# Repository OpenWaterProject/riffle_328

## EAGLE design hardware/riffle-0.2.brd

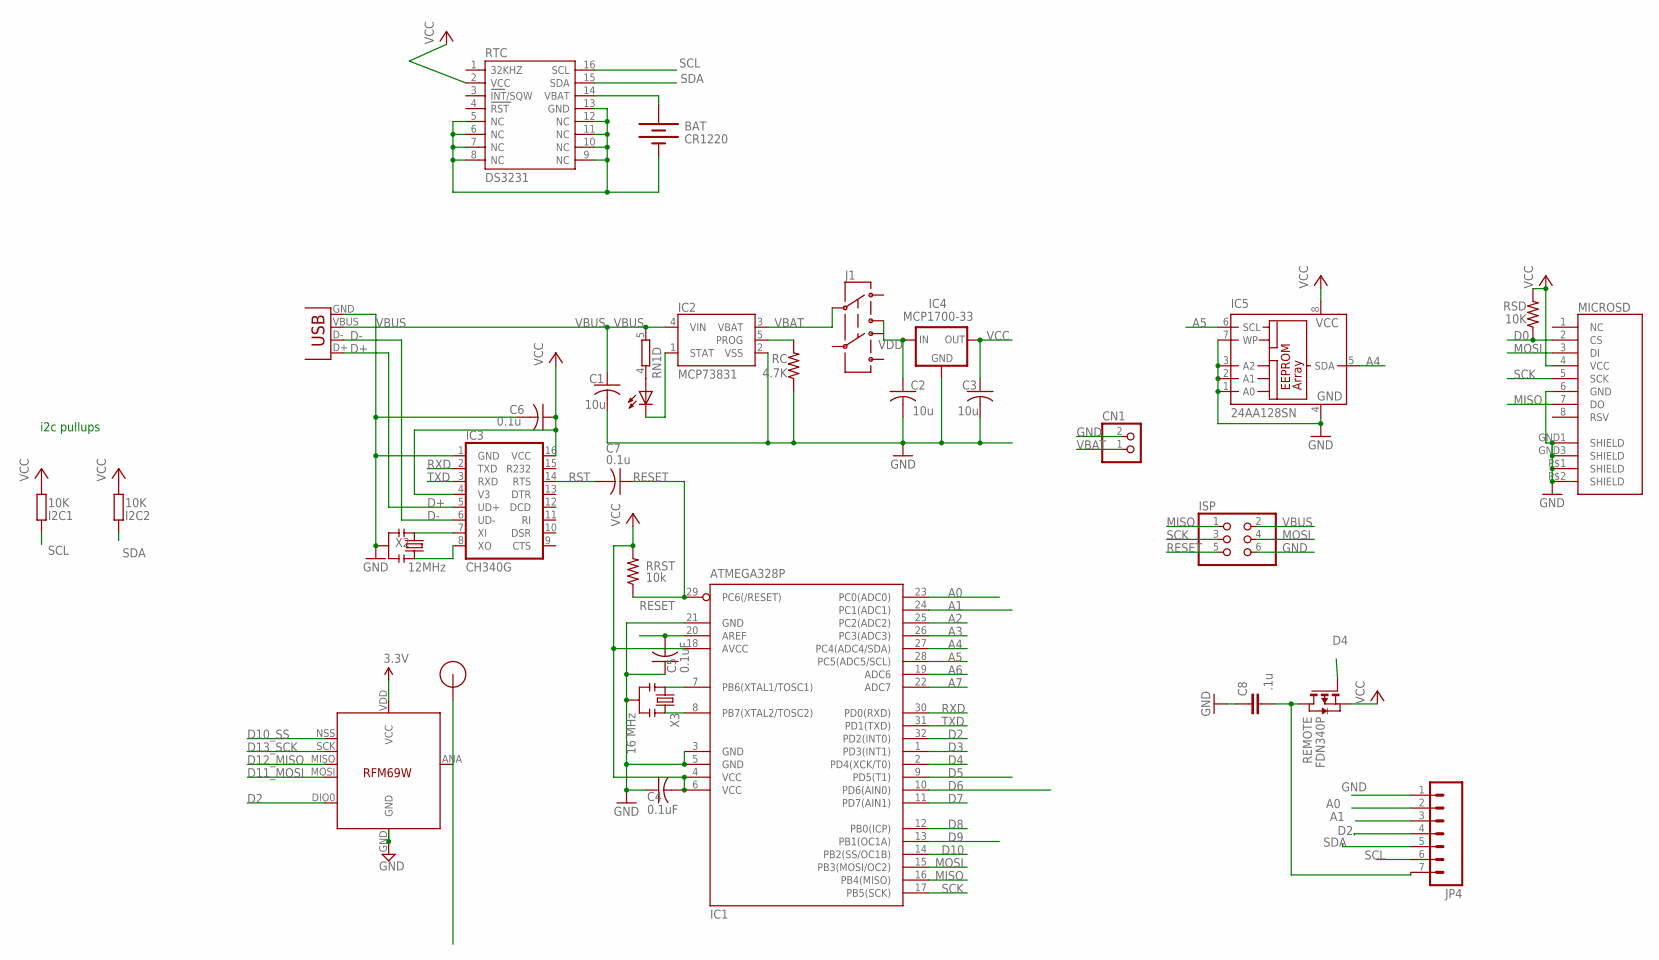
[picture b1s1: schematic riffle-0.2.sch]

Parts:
BAT: CR1220; BATTCON_12MM_SMT
C1, C2, C3: 10u; C0805K
C4, C5: 0.1uF; C0805K
C6, C7: 0.1u; C0805K
C8: .1u; C0805
CHG: 0805; CHIPLED_0805
CN1: JST_2PIN-SMT-RA; JST-PH-2-SMT-RA
I2C1, I2C2: 10K; R0805
IC1: ATMEGA328P; TQFP32-08
IC2: MCP73831; SOT23-5
IC3: CH340G; SO16
IC4: MCP1700-33; SOT89
IC5: 24AA128SN; SO-08
ISP: PINHD-2X3; 2X03
J1: AYZ0202
JP4: M07; 1X07
MICROSD: USD-SOCKETMICRO-SD-SOCKET-TAOBAO; MICRO-SD-SOCKET-TAOBAO
RC: 4.7K; R0805
REMOTE: FDN340P; SOT-23
RN1: 4R-NEXB38V; EXB38V
RRST: 10k; R0805
RSD: 10K; R0603
RTC: DS3231
U$3: RFM12B_ANTENNA; RFM12B-ANTENNA
U$5: RFM69; RFM69W-MINPADS
X1: USBSMD; USB-MINIB
X2: 12MHz; RESONATOR-SMD
X3: 16 MHz; RESONATOR-SMD

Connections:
A0: IC1.23 (PC0(ADC0)), JP4.2
A1: IC1.24 (PC1(ADC1)), JP4.3
A2: IC1.25 (PC2(ADC2))
A3: IC1.26 (PC3(ADC3)); also elsewhere on the board
A4: IC1.27 (PC4(ADC4/SDA)), IC5.5 (SDA)
A5: IC1.28 (PC5(ADC5/SCL)), IC5.6 (SCL)
A6: IC1.19 (ADC6)
A7: IC1.22 (ADC7)
AREF: C5.2, IC1.20 (AREF)
D0: MICROSD.2 (CS), RSD.1
D2: IC1.32 (PD2(INT0)), JP4.4, U$5.DIO0
D3: IC1.1 (PD3(INT1))
D4: IC1.2 (PD4(XCK/T0)), REMOTE.3 (G)
D5: IC1.9 (PD5(T1))
D6: IC1.10 (PD6(AIN0))
D7: IC1.11 (PD7(AIN1))
D8: IC1.12 (PB0(ICP))
D9: IC1.13 (PB1(OC1A))
D10: IC1.14 (PB2(SS/OC1B))
D10_SS: U$5.NSS (SEL)
D11_MOSI: U$5.MOSI
D12_MISO: U$5.MISO
D13_SCK: U$5.SCK
D+: IC3.5 (UD+), X1.D+
D-: IC3.6 (UD-), X1.D-
GND: BAT.P$1 (-), C1.2, C2.2, C3.2, C4.1, C5.1, C6.2, C8.1, CN1.2 (1), IC1.3 (GND), IC1.5 (GND), IC1.21 (GND), IC2.2 (VSS), IC3.1 (GND), IC4.1 (GND), IC5.1 (A0), IC5.2 (A1), IC5.3 (A2), IC5.4 (GND), IC5.7 (WP), ISP.6, JP4.1, MICROSD.6 (GND), MICROSD.GND1 (SHIELD), MICROSD.GND3 (SHIELD), MICROSD.P$1 (SHIELD), MICROSD.P$2 (SHIELD), RC.1, RTC.5 (NC), RTC.6 (NC), RTC.7 (NC), RTC.8 (NC), RTC.9 (NC), RTC.10 (NC), RTC.11 (NC), RTC.12 (NC), RTC.13 (GND), U$5.GND, X1.GND, X2.2, X3.2; also elsewhere on the board
MISO: IC1.16 (PB4(MISO)), ISP.1, MICROSD.7 (DO)
MOSI: IC1.15 (PB3(MOSI/OC2)), ISP.4, MICROSD.3 (DI)
unnamed: U$3.P$1, U$5.ANA (ANT)
unnamed: IC1.7 (PB6(XTAL1/TOSC1)), X3.1
unnamed: IC1.8 (PB7(XTAL2/TOSC2)), X3.3
unnamed: CHG.C, IC2.1 (STAT)
unnamed: IC2.5 (PROG), RC.2
unnamed: C8.2, JP4.7, REMOTE.1 (D)
unnamed: CHG.A, RN1.4 (1)
unnamed: IC3.7 (XI), X2.1
unnamed: IC3.8 (XO), X2.3
RESET: C7.1, IC1.29 (PC6(/RESET)), ISP.5, RRST.1
RST: C7.2, IC3.14 (RTS)
RTC_BATT: BAT.P$2 (+), RTC.14 (VBAT)
RXD: IC1.30 (PD0(RXD)), IC3.2 (TXD)
SCK: IC1.17 (PB5(SCK)), ISP.3, MICROSD.5 (SCK)
SCL: I2C1.2, JP4.6, RTC.16 (SCL)
SDA: I2C2.2, JP4.5, RTC.15 (SDA)
TXD: IC1.31 (PD1(TXD)), IC3.3 (RXD)
VBAT: CN1.1 (2), IC2.3 (VBAT), J1.2
VBUS: C1.1, IC2.4 (VIN), ISP.2, RN1.5 (2), X1.VBUS
VCC: C3.1, C4.2, C6.1, I2C1.1, I2C2.1, IC1.4 (VCC), IC1.6 (VCC), IC1.18 (AVCC), IC3.4 (V3), IC3.16 (VCC), IC4.3 (OUT), IC5.8 (VCC), MICROSD.4 (VCC), REMOTE.2 (S), RRST.2, RSD.2, RTC.2 (VCC), U$5.VDD (VCC)
VDD: C2.1, IC4.2 (IN), J1.1 (3)

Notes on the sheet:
i2c pullups

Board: 2 copper layers, 37 parts (1 on the bottom side), 35 nets, no tracks yet.

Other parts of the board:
C9: .1uF; C0805@1
JP1: 1X02
RM1, RM2: 10K; R0805

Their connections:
A3: C9.2, RM1.1, RM2.2; also elsewhere on the board
GND: C9.1, RM2.1; also elsewhere on the board

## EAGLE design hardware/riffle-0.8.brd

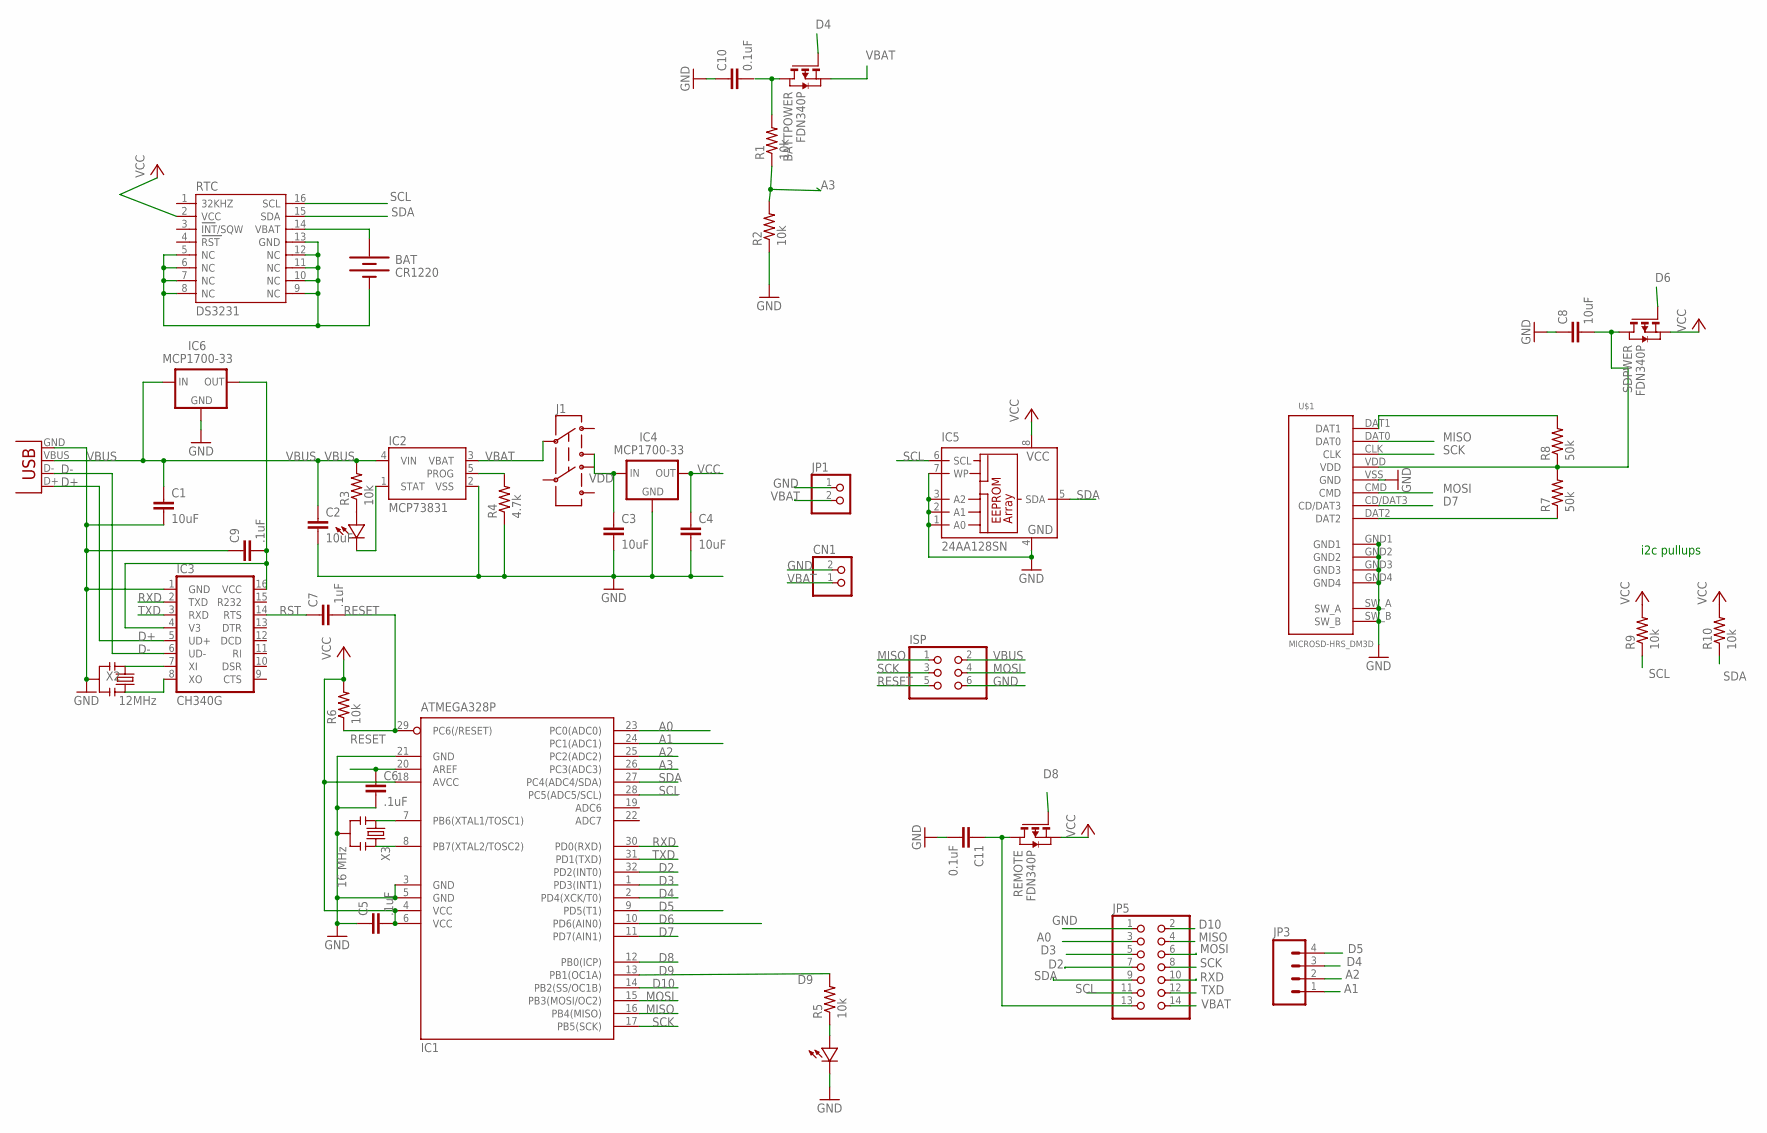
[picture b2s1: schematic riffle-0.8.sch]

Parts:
BAT: CR1220; BATTCON_12MM_SMT
BATTPOWER: FDN340P; SOT-23
C1, C2, C3, C4, C8: 10uF; 0402-CAP
C5, C6, C7, C9: .1uF; 0402-CAP
C10, C11: 0.1uF; 0402-CAP
CHG: LED0603; 0603-LED
CN1: JST_2PIN-SMT-RA; JST-PH-2-SMT-RA
IC1: ATMEGA328P; TQFP32-08
IC2: MCP73831; SOT23-5
IC3: CH340G; SO16
IC4, IC6: MCP1700-33; SOT89
IC5: 24AA128SN; SO-08
ISP: PINHD-2X3; 2X03
J1: AYZ0202
JP1: PINHD-1X2; 1X02
JP3: M04SMD; 1X04-SMD
JP5: PINHD-2X7; 2X07
R1, R2, R3, R5, R6, R9, R10: 10k; 0402-RES
R4: 4.7k; 0402-RES
R7, R8: 50k; 0402-RES
REMOTE: FDN340P; SOT-23
RTC: DS3231
SDPWER: FDN340P; SOT-23
STAT: LED0603; 0603-LED
U$1: MICROSD-HRS_DM3D; DM3D
X1: USBSMD; USB-MINIB
X2: 12MHz; RESONATOR-SMD
X3: 16 MHz; RESONATOR-SMD

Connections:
A0: IC1.23 (PC0(ADC0)), JP5.3
A1: IC1.24 (PC1(ADC1)), JP3.1
A2: IC1.25 (PC2(ADC2)), JP3.2
A3: IC1.26 (PC3(ADC3)), R1.1, R2.2
AREF: C6.1, IC1.20 (AREF)
D2: IC1.32 (PD2(INT0)), JP5.7
D3: IC1.1 (PD3(INT1)), JP5.5
D4: BATTPOWER.3 (G), IC1.2 (PD4(XCK/T0)), JP3.3
D5: IC1.9 (PD5(T1)), JP3.4
D6: IC1.10 (PD6(AIN0)), SDPWER.3 (G)
D7: IC1.11 (PD7(AIN1)), U$1.CD/DAT3
D8: IC1.12 (PB0(ICP)), REMOTE.3 (G)
D9: IC1.13 (PB1(OC1A)), R5.2
D10: IC1.14 (PB2(SS/OC1B)), JP5.2
D+: IC3.5 (UD+), X1.D+
D-: IC3.6 (UD-), X1.D-
GND: BAT.P$1 (-), C1.2, C2.2, C3.2, C4.2, C5.1, C6.2, C8.1, C9.1, C10.1, C11.2, CN1.2 (1), IC1.3 (GND), IC1.5 (GND), IC1.21 (GND), IC2.2 (VSS), IC3.1 (GND), IC4.1 (GND), IC5.1 (A0), IC5.2 (A1), IC5.3 (A2), IC5.4 (GND), IC5.7 (WP), IC6.1 (GND), ISP.6, JP1.1, JP5.1, R2.1, R4.1, RTC.5 (NC), RTC.6 (NC), RTC.7 (NC), RTC.8 (NC), RTC.9 (NC), RTC.10 (NC), RTC.11 (NC), RTC.12 (NC), RTC.13 (GND), STAT.MINUS, U$1.GND1, U$1.GND2, U$1.GND3, U$1.GND4, U$1.SW_A, U$1.SW_B, U$1.VSS (GND), X1.GND, X2.2, X3.2
MISO: IC1.16 (PB4(MISO)), ISP.1, JP5.4, U$1.DAT0
MOSI: IC1.15 (PB3(MOSI/OC2)), ISP.4, JP5.6, U$1.CMD
unnamed: CHG.PLUS, R3.1
unnamed: IC1.7 (PB6(XTAL1/TOSC1)), X3.1
unnamed: IC1.8 (PB7(XTAL2/TOSC2)), X3.3
unnamed: C8.2, R7.2, R8.1, SDPWER.1 (D), U$1.VDD
unnamed: CHG.MINUS, IC2.1 (STAT)
unnamed: IC2.5 (PROG), R4.2
unnamed: C11.1, JP5.13, REMOTE.1 (D)
unnamed: C9.2, IC3.4 (V3), IC3.16 (VCC), IC6.3 (OUT)
unnamed: IC3.7 (XI), X2.1
unnamed: IC3.8 (XO), X2.3
unnamed: BATTPOWER.1 (D), R1.2
unnamed: R8.2, U$1.DAT1
unnamed: R5.1, STAT.PLUS
unnamed: R7.1, U$1.DAT2
RESET: C7.2, IC1.29 (PC6(/RESET)), ISP.5, R6.1
RST: C7.1, IC3.14 (RTS)
RTC_BATT: BAT.P$2 (+), RTC.14 (VBAT)
RXD: IC1.30 (PD0(RXD)), IC3.2 (TXD), JP5.10
SCK: IC1.17 (PB5(SCK)), ISP.3, JP5.8, U$1.CLK
SCL: IC1.28 (PC5(ADC5/SCL)), IC5.6 (SCL), JP5.11, R9.1, RTC.16 (SCL)
SDA: IC1.27 (PC4(ADC4/SDA)), IC5.5 (SDA), JP5.9, R10.1, RTC.15 (SDA)
TXD: IC1.31 (PD1(TXD)), IC3.3 (RXD), JP5.12
VBAT: BATTPOWER.2 (S), CN1.1 (2), IC2.3 (VBAT), J1.2, JP1.2, JP5.14
VBUS: C1.1, C2.1, IC2.4 (VIN), IC6.2 (IN), ISP.2, R3.2, X1.VBUS
VCC: C4.1, C5.2, IC1.4 (VCC), IC1.6 (VCC), IC1.18 (AVCC), IC4.3 (OUT), IC5.8 (VCC), R6.2, R9.2, R10.2, REMOTE.2 (S), RTC.2 (VCC), SDPWER.2 (S)
VDD: C3.1, IC4.2 (IN), J1.1 (3)

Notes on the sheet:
i2c pullups

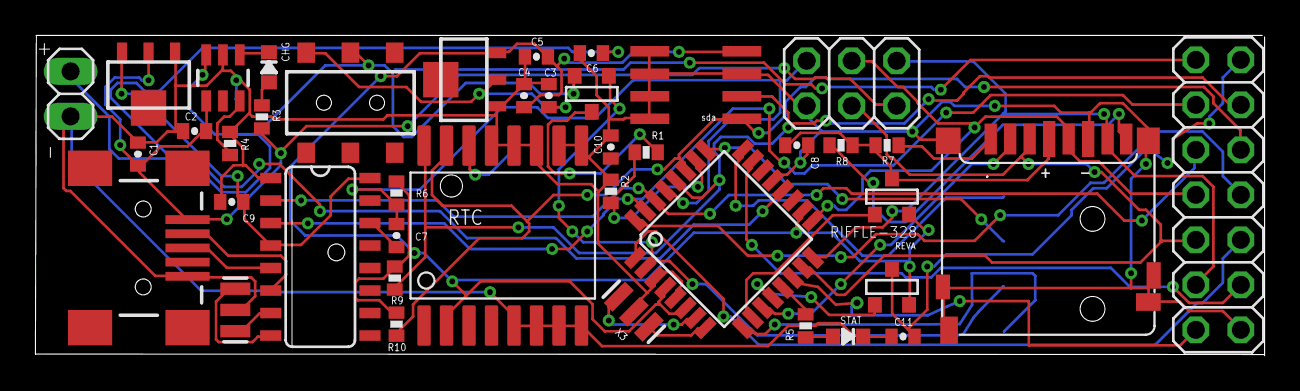
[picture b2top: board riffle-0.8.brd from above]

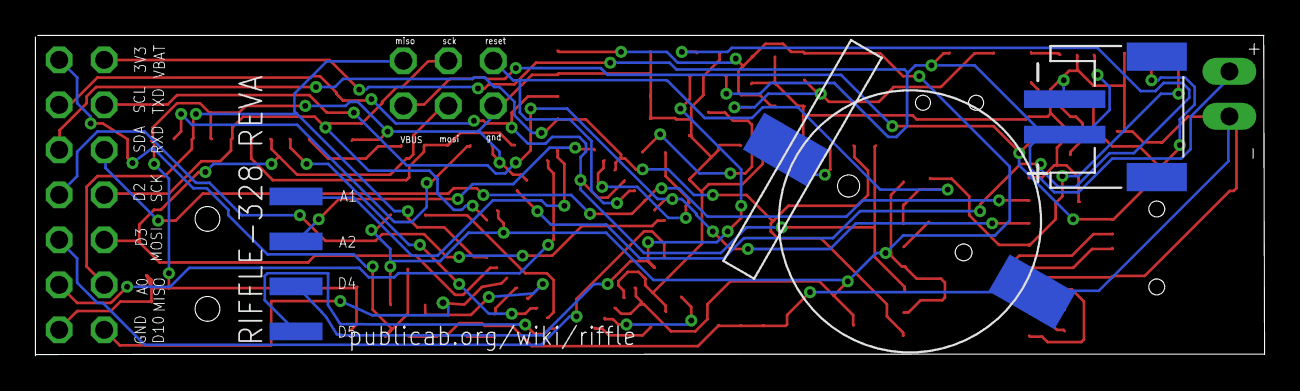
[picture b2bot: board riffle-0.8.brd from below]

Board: 2 copper layers, 69.4 x 18.1 mm, 44 parts (3 on the bottom side), 45 nets.

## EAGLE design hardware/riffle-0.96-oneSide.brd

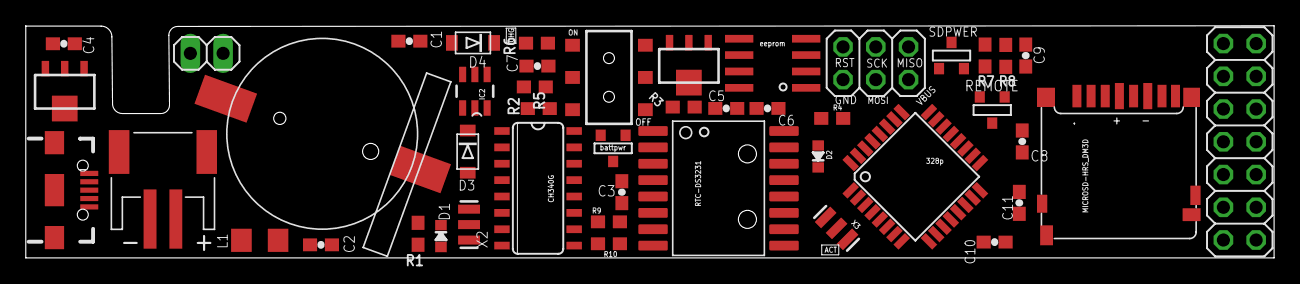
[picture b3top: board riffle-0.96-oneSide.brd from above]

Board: 2 copper layers, 96.9 x 18.0 mm, 47 parts (1 on the bottom side), 48 nets, no tracks yet.

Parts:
BAT: CR1220; BATTCON_12MM_SMT
BATTPOWER: FDN340P; SOT-23
C1, C4, C5, C6: 10uF; 0603-CAP
C2, C3, C7, C8, C9, C10, C11: 0.1uF; 0603-CAP
CN1: JST-PH-2-SMT-RA
D1, D2: LED0603; 0603-LED
D3, D4: SCHOTTKY; SOD-123FL
IC1: ATMEGA328P; TQFP32-08
IC2: MCP73831; SOT23-5
IC3: CH340G; SO16
IC4, IC6: MCP1700-33; SOT89
IC5: 24AA128SN; SO-08
ISP: 2X03
J1: AYZ0202
JP1: 1X02
JP3: 1X04-SMD
JP5: 2X07
L1: 500mA; R1206
R1, R3, R4, R5, R6, R9, R10: 10K; 0603-NO
R2: 4.7K; 0603-NO
R7, R8: 50K; 0603-NO
REMOTE: FDN340P; SOT-23
RTC-DS3231: DS3231
SDPWER: FDN340P; SOT-23
U$1: MICROSD-HRS_DM3D; DM3D
U$4: USB-AB-MICRO-SMD_V02_BOSS
X2: 12MHz; RESONATOR-SMD
X3: 16 MHz; RESONATOR-SMD

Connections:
A0: IC1.23, JP5.13
A1: IC1.24, JP3.1
A2: IC1.25, JP3.2
A3: IC1.26, R5.2, R6.1
AREF: C10.1, IC1.20
D2: IC1.32, JP5.7
D3: IC1.1, JP5.5
D4: BATTPOWER.3, IC1.2
D5: IC1.9, JP3.4
D6: IC1.10, SDPWER.3
D7: IC1.11, U$1.CD/DAT3
D8: IC1.12, REMOTE.3
D9: IC1.13, R4.2
D10: IC1.14, JP5.2
D+: IC3.5, U$4.D+1
D-: IC3.6, U$4.D-1
GND: BAT.P$1, C1.1, C2.2, C4.2, C5.2, C6.2, C7.1, C8.2, C9.1, C10.2, C11.1, CN1.2, D2.MINUS, IC1.3, IC1.5, IC1.21, IC2.2, IC3.1, IC4.1, IC5.1, IC5.2, IC5.3, IC5.4, IC5.7, IC6.1, ISP.6, JP1.1, JP3.3, JP5.1, R2.1, R5.1, RTC-DS3231.5, RTC-DS3231.6, RTC-DS3231.7, RTC-DS3231.8, RTC-DS3231.9, RTC-DS3231.10, RTC-DS3231.11, RTC-DS3231.12, RTC-DS3231.13, U$1.GND1, U$1.GND2, U$1.GND3, U$1.GND4, U$1.SW_A, U$1.SW_B, U$1.VSS, U$4.GND1, X2.2, X3.2
MISO: IC1.16, ISP.1, JP5.4, U$1.DAT0
MOSI: IC1.15, ISP.4, JP5.6, U$1.CMD
unnamed: D1.PLUS, R1.1
unnamed: IC1.7, X3.1
unnamed: IC1.8, X3.3
unnamed: C9.2, R7.1, R8.2, SDPWER.1, U$1.VDD
unnamed: D1.MINUS, IC2.1
unnamed: IC2.5, R2.2
unnamed: C8.1, JP5.3, REMOTE.1
unnamed: C2.1, IC3.4, IC3.16, IC6.3
unnamed: D3.A, L1.2
unnamed: IC3.7, X2.1
unnamed: IC3.8, X2.3
unnamed: D4.A, JP1.2
unnamed: BATTPOWER.1, C7.2, R6.2
unnamed: R7.2, U$1.DAT1
unnamed: D2.PLUS, R4.1
unnamed: R8.1, U$1.DAT2
unnamed: L1.1, U$4.VBUS1
RESET: C3.1, IC1.29, ISP.5, R3.1
RST: C3.2, IC3.14
RTC_BATT: BAT.P$2, RTC-DS3231.14
RXD: IC1.30, IC3.2, JP5.10
SCK: IC1.17, ISP.3, JP5.8, U$1.CLK
SCL: IC1.28, IC5.6, JP5.11, R9.1, RTC-DS3231.16
SDA: IC1.27, IC5.5, JP5.9, R10.1, RTC-DS3231.15
TXD: IC1.31, IC3.3, JP5.12
VBAT: BATTPOWER.2, CN1.1, D4.C, IC2.3, J1.2, JP5.14
VBUS: C1.2, C4.1, D3.C, IC2.4, IC6.2, ISP.2, R1.2
VCC: C6.1, C11.2, IC1.4, IC1.6, IC1.18, IC4.3, IC5.8, R3.2, R9.2, R10.2, REMOTE.2, RTC-DS3231.2, SDPWER.2
VDD: C5.1, IC4.2, J1.1

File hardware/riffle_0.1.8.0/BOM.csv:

Part,Details,Device,Package,Description,,MF,Cost per 100,cost,Source
BAT,CR1220,BATTERYBATTERY_12MM_SMT,BATTCON_12MM_SMT,Battery Holders,,,1.8,1.8,http://www.digikey.com/product-detail/en/1056TR/1056KCT-ND/4772075
"BATTPOWER, REMOTE, SDPWER",FDN340P,PMOSSOT23,SOT-23,MOS FET,,,0.24,0.72,http://www.digikey.com/product-detail/en/FDN340P/FDN340PCT-N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
"C1,C4,C5,C6",10uF,CAP0603-CAP,0603-CAP,Capacitor,*,,0.07,0.28,http://www.digikey.com/product-detail/en/CC0603MRX5R5BB106/3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
"C2,C3,C7,C8,C9,C10,C11",0.1uF,CAP0603-CAP,0603-CAP,Capacitor,*,,0.04,0.28,http://www.digikey.com/product-detail/en/C0603C104J4RACTU/39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
CN1,,JST_2PIN-SMT-RA,JST-PH-2-SMT-RA,JST 2-Pin Connectors of various flavors,,,0.4,0.4,http://www.digikey.com/product-detail/en/S2B-PH-SM4-TB%28LF%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
D1,LED0603,LED0603,0603-LED,,*,blue,0.23,0.23,http://www.digikey.com/product-detail/en/APT1608QBC%2FD/754-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
D2,LED0603,LED0603,0603-LED,,,yellow,0.17,0.17,http://www.digikey.com/product-detail/en/APT1608SYCK/754-112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
"D3, D4",SCHOTTKY,DIODE_SOD-123FL,SOD-123FL,Diode,,,0.22,0.44,http://www.digikey.com/product-detail/en/SM4002PL-TP/SM4002P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
IC1,ATMEGA328P,MEGA8-AI,TQFP32-08,MICROCONTROLLER,*,ATMEGA8-16AU,2.7,2.7,http://www.digikey.com/product-detail/en/ATMEGA328P-AU/ATMEG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
IC2,MCP73831,MCP73831,SOT23-5,Microchip's MCP73831,,,0.42,0.42,http://www.digikey.com/product-detail/en/MCP73831T-2ACI%2FOT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
IC3,CH340G,CH340G,SO16,,,,0.6,0.6,rui
"IC4, IC6",MCP1700-33,MCP1700SOT89,SOT89,VOLTAGE REGULATOR,*,,0.29,0.58,http://www.digikey.com/product-detail/en/0/MCP1700T3302EMBCT-ND
IC5,24AA128SN,24AA128SN,SO-08,Serial EEPROM,,24AA128-I/SN,0.5,0.5,http://www.digikey.com/product-detail/en/24AA128-I%2FSN/24AA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
ISP,,PINHD-2X3,2X03,PIN HEADER,,,,,(leave open for programming)
J1,AYZ0202,AYZ0202,AYZ0202,SPDT Slide Switch,,,1.07,1.07,http://www.digikey.com/product-detail/en/AYZ0202AGRLC/401-20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
JP1,,PINHD-1X2,1X02,PIN HEADER,,,,,(leave open)
JP3,,M04SMD,1X04-SMD,Header 4,,,,,(leave open)
JP5,,PINHD-2X7,2X07,PIN HEADER,,,0.98,0.98,http://www.digikey.com/product-detail/en/PPTC072LJBN-RC/S552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
L1,500mA,PTCFUSE-1206,R1206,"PTC fuses, resettable thermistors",,,0.17,0.17,http://www.digikey.com/product-detail/en/0ZCA0050FF2G/507-14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
"R1,R3,R4,R5,R6,R9,R10",10K,RESISTOR_0603_NOOUT,0603-NO,Resistors,*,,0.02,0.14,http://www.digikey.com/product-detail/en/CR0603-JW-103GLF/CR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
R2,4.7K,RESISTOR_0603_NOOUT,0603-NO,Resistors,*,,0.11,0.11,http://www.digikey.com/product-detail/en/MCT0603MD4701DP500/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
"R7,R8",50K,RESISTOR_0603_NOOUT,0603-NO,Resistors,*,,0.005,0.01,http://www.digikey.com/product-detail/en/RC0603JR-07100RL/31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
RTC-DS3231,DS3231,DS3231,DS3231,,,,6.3,6.3,http://www.digikey.com/product-detail/en/DS3231S%23/DS3231S%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
U$1,MICROSD-HRS_DM3D,MICROSD-HRS_DM3D,DM3D,,*,,1.5,1.5,http://www.digikey.com/product-detail/en/DM3D-SF/HR1941CT-ND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
U$4,,"USB-AB""",USB-AB-MICRO-SMD_V02_BOSS,This is a USB AB connector that is compatible with USB OTG. i.e. this connector can serve as a host or device,,,0.6,0.6,http://www.digikey.com/product-detail/en/10104111-0001LF/609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
X2,12MHz,RESONATORSMD,RESONATOR-SMD,Resonator,,X,0.4,0.4,https://www.digikey.com/product-detail/en/CSTCE12M0G55-R0/49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
X3,16 MHz,RESONATORSMD,RESONATOR-SMD,Resonator,*,,0.32,0.32,http://www.digikey.com/product-detail/en/CSTCE16M0V53-R0/490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

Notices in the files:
parts and their libraries:
SparkFun-Connectors: Licensing: Creative Commons ShareAlike 4.0 International - https://creativecommons.org/licenses/by-sa/4.0
microbuilder: This work is placed in the public domain, and may be freely used for commercial and non-commercial work with the following conditions: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
